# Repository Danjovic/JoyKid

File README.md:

# Joy Kid 

This project started as an exercise of passing and receiving parameters using CALL function, but evolved to a hardware prototype using a microcontroller that sends data through the MSX joystick port in order to emulate the MSX  [Sensor Kid](https://www.msx.org/wiki/Micomsoft_Sensor_Kid) Interface.

## Protocol
The circuit uses lightweight protocol that transfers sensor data using nibbles. The transfer is commanded by pin 8 (pulse) and the data transfer is paced by pin 7 (trigger B). Pin 6 (trigger A) is used both by the microcontroller to provide a 'ready' signal to the MSX and also to get PORT0/1 data. 

### Waveform

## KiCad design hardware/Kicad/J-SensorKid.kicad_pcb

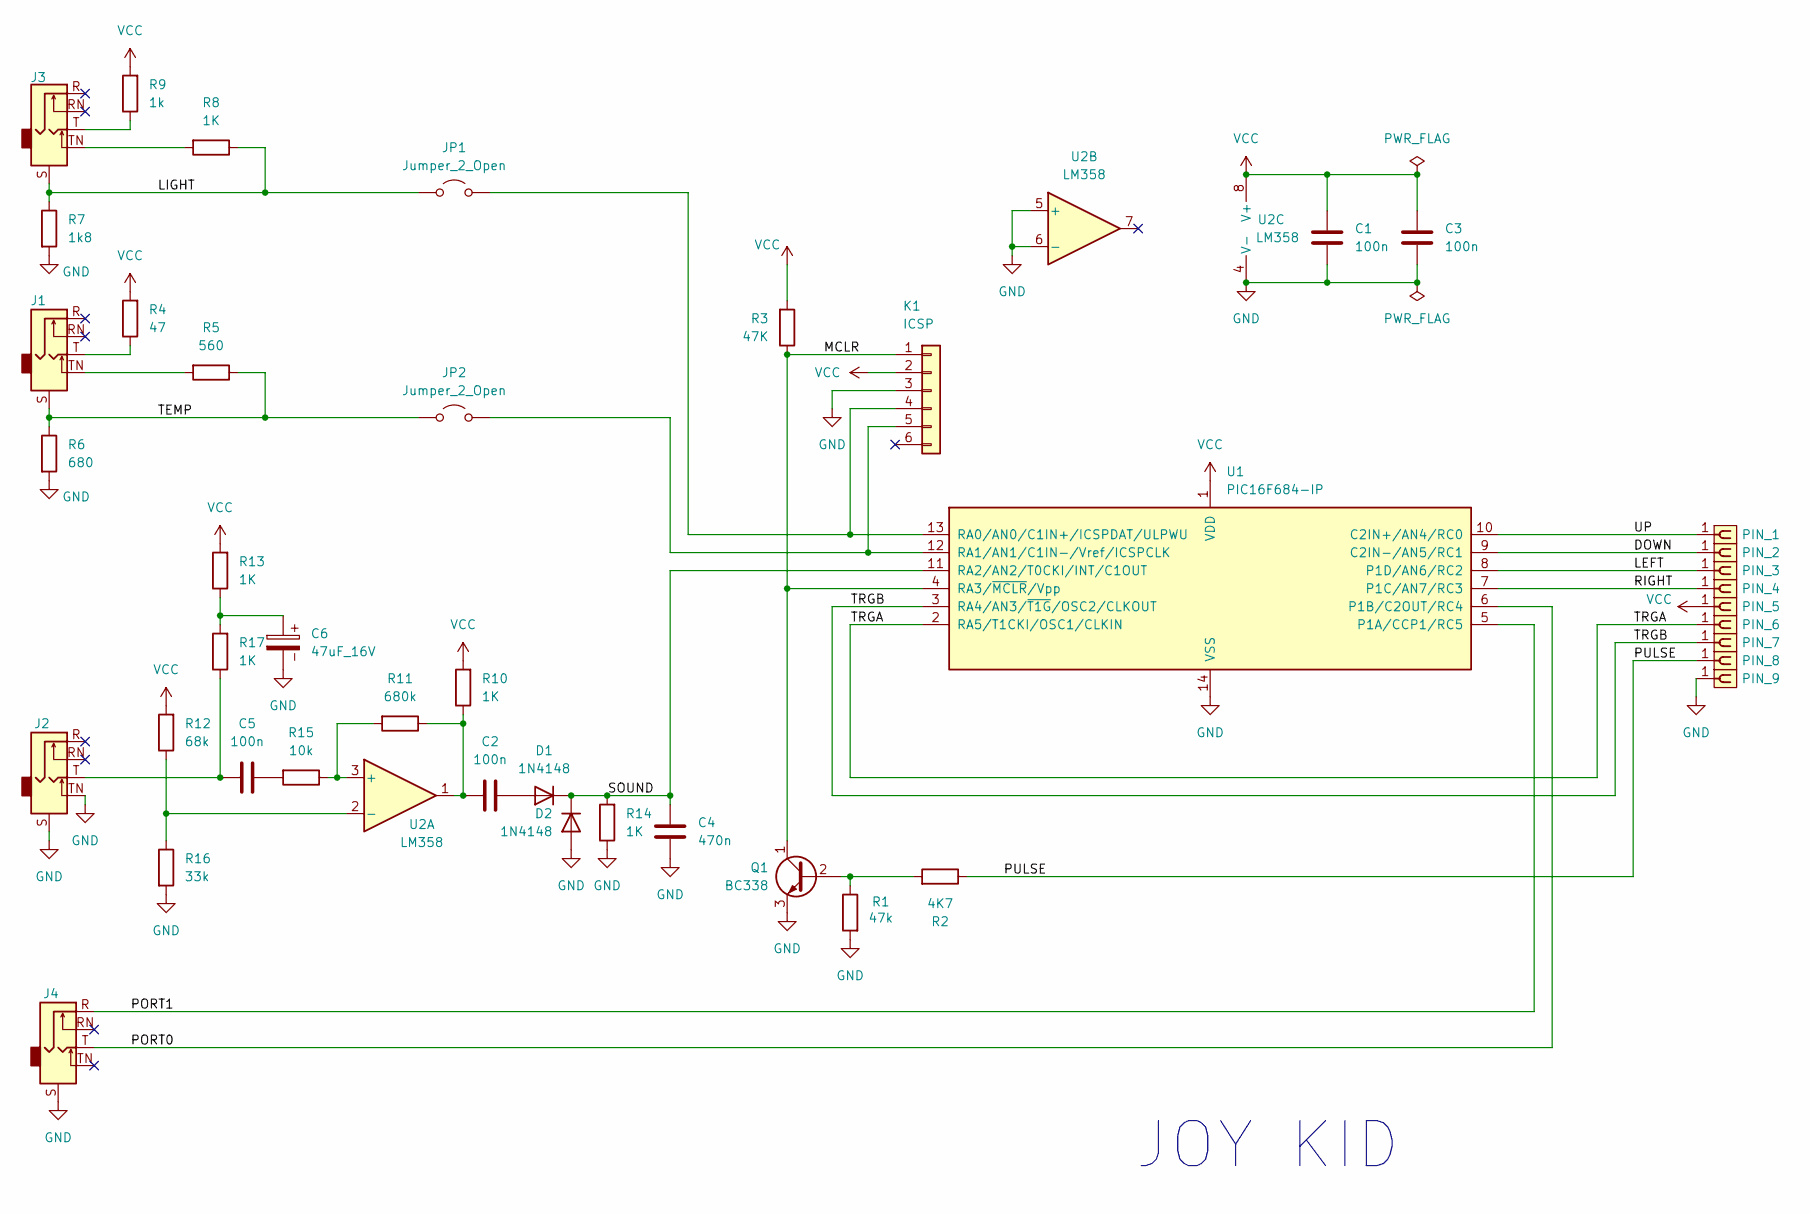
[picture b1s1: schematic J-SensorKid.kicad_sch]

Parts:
C1, C2, C3, C5: 100n; C_Disc_D6.0mm_W2.5mm_P5.00mm
C4: 470n; C_Disc_D6.0mm_W4.4mm_P5.00mm
C6: 47uF_16V; CP_Radial_D5.0mm_P2.00mm
D1, D2: 1N4148; D_DO-35_SOD27_P7.62mm_Horizontal
J1, J2, J3, J4: AudioJack2_Ground_Switch; Jack_3.5mm_CUI_SJ1-3535NG_Horizontal
JP1, JP2: Jumper_2_Open; PinHeader_1x02_P2.54mm_Vertical
K1: ICSP; PinHeader_1x06_P2.54mm_Vertical
PIN_1, PIN_2, PIN_3, PIN_4, PIN_5, PIN_6, PIN_7, PIN_8, PIN_9: PINHD_1x1_Female; PinSocket_1x01_P2.54mm_Vertical
Q1: BC338; TO-92L
R1: 47k; R_Axial_DIN0204_L3.6mm_D1.6mm_P7.62mm_Horizontal
R2: 4K7; R_Axial_DIN0204_L3.6mm_D1.6mm_P7.62mm_Horizontal
R3: 47K; R_Axial_DIN0204_L3.6mm_D1.6mm_P7.62mm_Horizontal
R4: 47; R_Axial_DIN0204_L3.6mm_D1.6mm_P7.62mm_Horizontal
R5: 560; R_Axial_DIN0204_L3.6mm_D1.6mm_P7.62mm_Horizontal
R6: 680; R_Axial_DIN0204_L3.6mm_D1.6mm_P7.62mm_Horizontal
R7: 1k8; R_Axial_DIN0204_L3.6mm_D1.6mm_P7.62mm_Horizontal
R8, R10, R13, R14, R17: 1K; R_Axial_DIN0204_L3.6mm_D1.6mm_P7.62mm_Horizontal
R9: 1k; R_Axial_DIN0204_L3.6mm_D1.6mm_P7.62mm_Horizontal
R11: 680k; R_Axial_DIN0204_L3.6mm_D1.6mm_P7.62mm_Horizontal
R12: 68k; R_Axial_DIN0204_L3.6mm_D1.6mm_P7.62mm_Horizontal
R15: 10k; R_Axial_DIN0204_L3.6mm_D1.6mm_P7.62mm_Horizontal
R16: 33k; R_Axial_DIN0204_L3.6mm_D1.6mm_P7.62mm_Horizontal
U1: PIC16F684-IP; DIP-14_W7.62mm
U2: LM358; DIP-8_W7.62mm

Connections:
/DOWN: PIN_2.1, U1.9 (C2IN-/AN5/RC1)
/LEFT: PIN_3.1, U1.8 (P1D/AN6/RC2)
/LIGHT: J3.S, JP1.1 (A), R7.1, R8.1
/MCLR: K1.1, Q1.1 (C), R3.1, U1.4 (RA3/~MCLR/Vpp)
/PORT0: J4.T, U1.6 (P1B/C2OUT/RC4)
/PORT1: J4.R, U1.5 (P1A/CCP1/RC5)
/PULSE: PIN_8.1, R2.1
/RIGHT: PIN_4.1, U1.7 (P1C/AN7/RC3)
/SOUND: C4.2, D1.1 (K), D2.1 (K), R14.2, U1.11 (RA2/AN2/T0CKI/INT/C1OUT)
/TEMP: J1.S, JP2.1 (A), R5.1, R6.1
/TRGA: PIN_6.1, U1.2 (RA5/T1CKI/OSC1/CLKIN)
/TRGB: PIN_7.1, U1.3 (RA4/AN3/~T1G/OSC2/CLKOUT)
/UP: PIN_1.1, U1.10 (C2IN+/AN4/RC0)
GND: C1.2, C3.2, C4.1, C6.2, D2.2 (A), J2.S, J2.TN, J4.S, K1.3, PIN_9.1, Q1.3 (E), R1.2, R6.2, R7.2, R14.1, R16.2, U1.14 (VSS), U2.4 (V-), U2.5 (+), U2.6 (-)
unnamed: C2.1, R10.1, R11.1, U2.1
unnamed: C5.1, J2.T, R17.1
unnamed: C5.2, R15.2
unnamed: C6.1, R13.1, R17.2
unnamed: C2.2, D1.2 (A)
unnamed: J1.T, R4.1
unnamed: J1.TN, R5.2
unnamed: J3.T, R9.1
unnamed: J3.TN, R8.2
unnamed: JP1.2 (B), K1.4, U1.13 (RA0/AN0/C1IN+/ICSPDAT/ULPWU)
unnamed: JP2.2 (B), K1.5, U1.12 (RA1/AN1/C1IN-/Vref/ICSPCLK)
unnamed: Q1.2 (B), R1.1, R2.2
unnamed: R11.2, R15.1, U2.3 (+)
unnamed: R12.1, R16.1, U2.2 (-)
VCC: C1.1, C3.1, K1.2, PIN_5.1, R3.2, R4.2, R9.2, R10.2, R12.2, R13.2, U1.1 (VDD), U2.8 (V+)

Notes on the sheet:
JOY KID

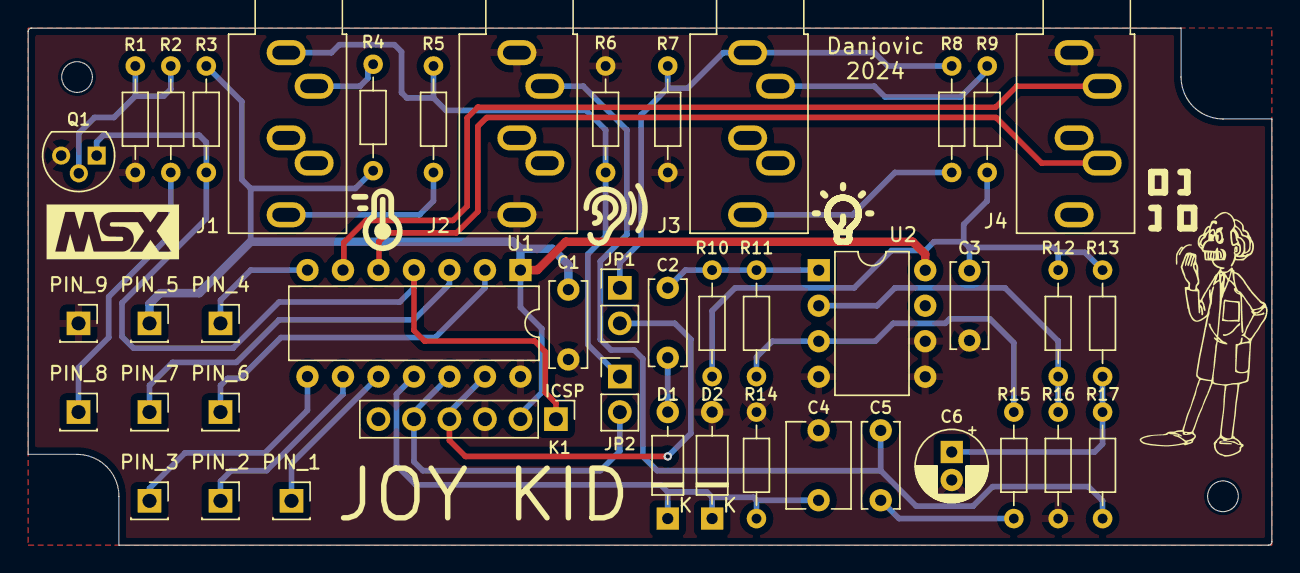
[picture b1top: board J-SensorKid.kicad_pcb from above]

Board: 2 copper layers, 89.0 x 37.0 mm, 47 parts (0 on the bottom side), 29 nets.

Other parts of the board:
MH1, MH2: MountingHole_2.2mm_M2_DIN965
PCB1: PB-082_1

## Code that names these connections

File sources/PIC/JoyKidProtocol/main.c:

/*
     ____.              ____  __.__    .___
    |    | ____ ___.__.|    |/ _|__| __| _/
    |    |/  _ <   |  ||      < |  |/ __ | 
/\__|    (  <_> )___  ||    |  \|  / /_/ | 
\________|\____// ____||____|__ \__\____ | 
                \/             \/       \/ 
  Sensor Kid for the Joystick port 
  Danjovic 2024 
*/

/* Pinout

   PIC16F688
                 +--___--+ 
           +5V --|1    14|-- GND                          
     TRG-A RA5 --|2    13|-- RA0 LIGHT       \ 
     TRG-B RA4 --|3    12|-- RA1 TEMPERATURE | Sensors  
     PULSE RA3 --|4    11|-- RA2 SOUND       /
     PORT1 RC5 --|5    10|-- RC0 UP
     PORT0 RC4 --|6     9|-- RC1 DOWN                  
     RIGHT RC3 --|7     8|-- RC2 LEFT     
                 +-------+  
*/


/* JoyKid Protocol

 GETTING ATTENTION
 - MSX rise pin 8 to marks the beginning of a transfer and wait for the JoyKid to acknowledge by lowering pin 6 
 - Joykid regognizes the ATT request, reads the values of its analog sensors and then drop pin 6 
 
 Now both MSX and JoyKid are ready to TRANSFERING DATA 
 
 - MSX drops pin 7 to mark the start of a data frame.
 - JoyKid recognize the sof mark, writes 1st lower nibble and release pin 6
 - MSX reads the 1st lower nibble, then rise pin 7
 
 - Joykid recognize the change and write the 1st higher nibble
 - MSX reads the 1st higher nibble, then drop pin 7 and write PORT0 value 
 - Joykid recognize the change, read PORT0 value and and write the 2nd lower nibble
 - MSX reads the 2nd lower nibble, then rise pin 7
 - Joykid recognize the change and write the 2nd higher nibble
 - MSX reads the 1st higher nibble, then drop pin 7 and write PORT1 value 
 - Joykid recognize the change, read PORT1 value and and write the 3rd lower nibble
 - MSX reads the 3rd lower nibble, then rise pin 7
 - Joykid recognize the change and write the 3rd higher nibble
 - MSX reads the 3rd higher nibble, then drop pin 8 to finalize the transfer
 - Joykid recognize the change, release the data lines populate the outputs and wait for the start of a new transfer
 
 
 
 
; Protocol
;        ____________________________________________
;  8 ___/ ATT                                        \_______
;    ________________        ____      ____      ____________
;  7                 \_sof__/    \____/    \____/           
;    _________         __________                     _______ 
;  6          \_ack___/ release  |  PORT 0 |  PORT 1 |
;    
;  1 ------------------| d0 | d4 | d0 | d4 | d0 | d4 |-------
;  2 ------------------| d1 | d5 | d1 | d4 | d5 | d5 |-------
;  3 ------------------| d2 | d6 | d2 | d4 | d6 | d6 |-------
;  4 ------------------| d3 | d7 | d3 | d4 | d7 | d7 |-------
;
*/ 


//    _ _ _                 _        
//   | (_) |__ _ _ __ _ _ _(_)___ ___
//   | | | '_ \ '_/ _` | '_| / -_|_-<
//   |_|_|_.__/_| \__,_|_| |_\___/__/
//                                   


#include <pic16f688.h>
#include <stdint.h>
#include <stdbool.h>

// Fuse setting 
uint16_t __at _CONFIG configWord = _INTRC_OSC_NOCLKOUT & _CPD_OFF &  _CP_OFF &  _MCLRE_OFF & _WDT_OFF & _PWRTE_ON; // watchdog off

//       _      __ _      _ _   _             
//    __| |___ / _(_)_ _ (_) |_(_)___ _ _  ___
//   / _` / -_)  _| | ' \| |  _| / _ \ ' \(_-<
//   \__,_\___|_| |_|_||_|_|\__|_\___/_||_/__/
//                                            
#define LIGHT  0  
#define TEMP   1 
#define SOUND  2
 
#define LIGHT_CHANNEL (0<<2)  // masks for ADC
#define TEMP_CHANNEL  (1<<2)  // 
#define SOUND_CHANNEL (2<<2)  //

#define BIT_PORT0 0
#define BIT_PORT1 1

#define PORT0  RC4
#define PORT1  RC5

#define PULSE  RA3
#define TRGB   RA4
#define TRGA   RA5

#define PIN8  RA3
#define PIN7  RA4
#define PIN6  RA5
#define DIR_PIN6 TRISA5

#define Att()    PULSE==0
#define NotAtt() PULSE!=0
  
#define ReleasePin6()   do { DIR_PIN6 = 1;  PIN6 = 1; } while (0)
#define DropPin6()      do { DIR_PIN6 = 0;  PIN6 = 0; } while (0)

#define ReleaseOutputs() PORTC|=0x0f


//                 _      _    _        
//   __ ____ _ _ _(_)__ _| |__| |___ ___
//   \ V / _` | '_| / _` | '_ \ / -_|_-<
//    \_/\__,_|_| |_\__,_|_.__/_\___/__/
//      
bool Port0,Port1;
uint8_t lightSensor,temperatureSensor,soundSensor;

//                 _       _
//    _ __ _ _ ___| |_ ___| |_ _  _ _ __  ___ ___
//   | '_ \ '_/ _ \  _/ _ \  _| || | '_ \/ -_|_-<
//   | .__/_| \___/\__\___/\__|\_, | .__/\___/__/
//   |_|                       |__/|_|
void initHardware(void);
uint8_t readADC (uint8_t channelMask); 
void transferData(void);

//               _      
//    _ __  __ _(_)_ _  
//   | '  \/ _` | | ' \ 
//   |_|_|_\__,_|_|_||_|
//                      


void main (void)
{
    initHardware();
	
	// wait initially for Pin8 be unactive 
	while ( Att() ) {};

// - MSX rise pin 8 to marks the beginning of a transfer 
	for (;;) {
// - Joykid regognizes the ATT request, ...
		while (NotAtt()) { } ; // wait for the ATT
        transferData();
		ReleasePin6();
		ReleaseOutputs();
	}
}





void transferData(void)	{
	
	    uint8_t tempC = PORTC & 0xf0;
// ..., reads the values of its analog sensors and then drop pin 6 		
		// Read ADC values ( ~130us to read the three channels )
		lightSensor = readADC(LIGHT_CHANNEL);  
		temperatureSensor = readADC(TEMP_CHANNEL) ;
		soundSensor = readADC(SOUND_CHANNEL);
		DropPin6();	  
		
// - MSX drops pin 7 to mark the start of a data frame.
// - JoyKid recognize the sof mark, writes 1st lower nibble and release pin 6		
		while (PIN7) { if (NotAtt()) return; };
		PORTC = tempC | (lightSensor & 0x0f);
		ReleasePin6();
		
// - MSX reads the 1st lower nibble, then rise pin 7
// - Joykid recognize the change and write the 1st higher nibble
        while (PIN7==0) { if (NotAtt()) return; };
		PORTC = tempC | (lightSensor>>4);

// - MSX reads the 1st higher nibble, then drop pin 7 and write PORT0 value 
// - Joykid recognize the change, read PORT0 value and and write the 2nd lower nibble
		while (PIN7) { if (NotAtt()) return; };
		PORTC = tempC | (temperatureSensor & 0x0f);
		Port0 = PIN6; //(PIN6? 1: 0);   


// - MSX reads the 2nd lower nibble, then rise pin 7
// - Joykid recognize the change and write the 2nd higher nibble
        while (PIN7==0) { if (NotAtt()) return; };
		PORTC = tempC | (temperatureSensor>>4);


// - MSX reads the 1st higher nibble, then drop pin 7 and write PORT1 value 
// - Joykid recognize the change, read PORT1 value and and write the 3rd lower nibble
		while (PIN7) { if (NotAtt()) return; };
		PORTC = tempC | (soundSensor & 0x0f);
		Port1 = PIN6; //(PIN6? 1: 0);   


// - MSX reads the 3rd lower nibble, then rise pin 7
// - Joykid recognize the change and write the 3rd higher nibble
        while (PIN7==0) { if (NotAtt()) return; };
		PORTC = tempC | (soundSensor>>4);

// - MSX reads the 3rd higher nibble, then drop pin 8 to finalize the transfer
// - Joykid recognize the change, release the data lines populate the outputs and wait for the start of a new transfer
        while ( Att() ) {} ;  // 
		PORT0 = Port0;
		PORT1 = Port1;			 
}

uint8_t readADC (uint8_t channelMask) {
	//ADCON0 = (ADCON0 & 0b11100011) | channelMask ;  // select channel
 	ADCON0 = channelMask | _ADON;
	TMR0 = 216;         // preset for timer register
	TMR0IF = 1;  // clear interrupt flag
	while (!TMR0IF) {}; // wait 20us for sample/hold
	GO_NOT_DONE = 1;          // start the conversion
	while (GO_NOT_DONE) {};      // wait for conversion to end
	return ADRESH;
}

void initHardware(void) {
  // Initialize clock
   IRCF0 = 1 ;  // 8MHz -> IRCF[2..0] = 111 ( default 110 on startup )
   
   // Initialize I/O ports
   CMCON0 = ( _CM2 | _CM1 | _CM0); // analog comparators off, pins as I/O 
  
   TRISC=0b11000000; // RC0-RC5 as outputs
   PORTC=0b00001111; // U/D/L/R unactive(high), PORT0 PORT1 unactive (low)
    
   TRISA=0b11111111; // RA0-RA5 as inputs
   PORTA=0b00000000; // All low   
   
   // Initialize A/D converter
   ANSEL  = (1<<2)|(1<<1)|(1<<0); // Configure analog/digital I/Os (ANSEL)
   ADCON0 = _ADON;      //  ADFM = 0 , ADON = 1
   ADCON1 = 0b01110000;	 //  ADCS1 [2..0] = x11 -> FRC Internal 500KHz oscillator
   //ADON = 1;

}

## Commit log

2024-12-04 updated files
2024-12-04 Delete hardware/Kicad directory
    Reorganization
